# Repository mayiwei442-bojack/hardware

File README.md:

# ACID ALLOY / 酸性合金

多输入桌面控制器的外观设计、Blender 装配模型与交互展示网站。包含 13 个机械按键、旋钮、摇杆、触摸输入和 RGB 灯光的结构与展示资料。

## 项目文件

| 目录 | 内容 |
| --- | --- |
| [`website/`](website/) | 五章节产品展示网站、二维交互工作台、七步制作流程演示、测试与截图 |
| [`modeling/assets/`](modeling/assets/) | Blender 主模型、四种外观方案和阶段存档 |
| [`modeling/`](modeling/) | 渲染、印花贴图、建模脚本、尺寸参考、验收记录和操作说明 |
| [`device/`](device/) | 硬件设计、制造文件、打印模型、固件与配套工具 |

## Blender 方案

| 方案 | 文件 | 预览 |
| --- | --- | --- |
| 基础装配 | [`MacroPad.blend`](modeling/assets/MacroPad.blend) | 装配、器件和交互控制 |
| 酸性合金 | [`MacroPad_AcidAlloy.blend`](modeling/assets/MacroPad_AcidAlloy.blend) |  |
| 电光瓷器 | [`MacroPad_ElectricPorcelain.blend`](modeling/assets/MacroPad_ElectricPorcelain.blend) |  |
| 超频仪器 | [`MacroPad_OverclockInstrument.blend`](modeling/assets/MacroPad_OverclockInstrument.blend) |  |
| 反叛玩具 | [`MacroPad_RebelToy.blend`](modeling/assets/MacroPad_RebelToy.blend) |  |

使用 Blender 打开 `.blend` 文件；成品印花贴图已内嵌。历史验收记录保留当时的校验值和本机路径；可读项目名已统一替换，本次整理未重新执行 Blender 验收。

## 网站本地启动

```powershell
cd website
npm ci
npm run dev
```

浏览器打开 `http://localhost:3100`。网站目前以二维交互演示为主，正式 GLB、产品照片等素材的接入状态见 [`website/docs/assets.md`](website/docs/assets.md)。制作流程为浏览器内模拟。

## 制造资料

- [Gerber 制造文件](device/hw/v1/fab/keyboard-gerbers.zip)
- [BOM 元件清单](device/hw/v1/fab/keyboard-bom.csv)
- [SMT 贴片坐标](device/hw/v1/fab/keyboard-smt.csv)
- [打印与可编辑机械模型](device/hw/v1/mechanical/)
- [制造说明](device/hw/v1/fab/README.md)

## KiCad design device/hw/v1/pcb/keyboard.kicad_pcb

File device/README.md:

<picture>
  <source media="(prefers-color-scheme: dark)" srcset="site/public/assets/wordmark-dark.png">
  
</picture>

# keyboard

An open-source hardware recreation of OpenAI's **Codex Micro** macropad — 13 low-profile keys, a rotary encoder, an analog joystick, a capacitive touch pad, and per-key + underglow RGB on a wired USB-C board built around an STM32F072.

*The finished board — read the [launch post](https://github.com/mayiwei442-bojack/hardware/blog/keyboard-launch/) for the full story.*

**The PCB is written, not drawn.** The entire schematic is source code in [**CoHDL**](https://cohdl.org), an open-source, AI-native hardware description language. The compiler type-checks the design — units, pin-connection obligations, power integrity — and emits the netlist, BOM, footprints and layout constraints you can inspect under [`hw/v1/out/`](hw/v1/out/).

🌐 **https://github.com/mayiwei442-bojack/hardware** · 🖨️ **[Printable case on MakerWorld](https://makerworld.com/en/models/3163016-keyboard#profileId-3599737)** ([中国站](https://makerworld.com.cn/zh/models/2838721-keyboard-kai-yuan-jian-pan))

## Designed in CoHDL

This board was designed in [**CoHDL**](https://cohdl.org), an open-source hardware description language that makes schematic (PCB) design AI-native: a board is a program — typed, checked, and compiled. In CoHDL, the design in [`hw/v1/src/`](hw/v1/src/) *is* the schematic; the compiler is the oracle that grades it.

**CoHDL is open source.** Visit [cohdl.org](https://cohdl.org) to explore the language, or browse and contribute to the compiler and libraries on GitHub. This repository also checks in the complete compiler outputs under `hw/*/out/`, so the generated hardware design remains directly inspectable.

Questions about CoHDL, the hardware source, or building a board of your own? [Join the CoHDL and keyboard community on Discord](https://discord.gg/x7DXPvK66).

## What's inside

| Path | Contents |
|---|---|
| [`hw/v1/src/`](hw/v1/src/) | The PCB as CoHDL source: `main.cohdl` (top-level design), `keyboard_parts.cohdl` (datasheet-verified part bindings), `footprints.cohdl`, `pads.cohdl` |
| [`hw/v1/out/`](hw/v1/out/) | Checked-in compiler output: KiCad netlist (`keyboard.net`), BOM (`keyboard-bom.csv`), SMT placement (`keyboard-smt.csv`), `.kicad_mod` footprints, layout constraints (`keyboard-layout.json`) |
| [`hw/v1/pcb/`](hw/v1/pcb/) | The routed board — `keyboard.kicad_pcb` + KiCad project (design rules) |
| [`hw/v1/fab/`](hw/v1/fab/) | Manufacturing package: Gerber/drill zip, assembly BOM, SMT placement CSV — see [`hw/v1/fab/README.md`](hw/v1/fab/README.md) |
| [`hw/v1/mechanical/`](hw/v1/mechanical/) | Board outline (DXF) plus the printable enclosure parts — case, rotary knob, joystick cap, shipping tray and a solder-assembly jig, as editable Fusion 360 `.f3d` and ready-to-slice `.3mf`. Also published as a print profile on [MakerWorld](https://makerworld.com/en/models/3163016-keyboard#profileId-3599737) ([中国站](https://makerworld.com.cn/zh/models/2838721-keyboard-kai-yuan-jian-pan)) |
| [`hw/v1/docs/`](hw/v1/docs/) | Manufacturer datasheets for every active, connector, and electromechanical part in the BOM, with sourcing/verification notes — see [`hw/v1/docs/README.md`](hw/v1/docs/README.md) |
| [`layout/`](layout/) | The bootloader/firmware/host contract: flash and RAM map, image header, handoff words, HID update protocol, CRC-32 — `no_std`, shared by `fw`, `boot`, `app` and `scripts/` |
| [`boot/`](boot/) | Resident 24 KiB bootloader at 0x08000000: validates the application by length and CRC-32 before every start and offers a driverless USB HID update mode, so an interrupted update never bricks the pad. See [`boot/README.md`](boot/README.md) |
| [`fw/`](fw/) | Firmware — Rust + [embassy](https://embassy.dev) on STM32F072CB: key matrix, twin WS2812 chains, USB HID + vendor interface, driverless updates through the resident bootloader (ROM DFU kept for migration and recovery), and an opt-in **Codex Micro compat mode** (the pad boots with the Codex Micro's USB identity and speaks ChatGPT Desktop's device protocol so the desktop app drives it natively — confirmed with Codex desktop 26.825 on macOS). See [`fw/README.md`](fw/README.md) |
| [`app/`](app/) | Companion desktop app — Rust + [GPUI](https://gpui.rs), with a crisp 8-bit visual system: device dashboard, live connection state, and button-free firmware updates over USB. See [`app/README.md`](app/README.md) |

## Hardware (v1)

- **MCU:** STM32F072CBT6 (Cortex-M0), 8 MHz HSE crystal, 2×3 SWD debug socket
- **Keys:** 13× Kailh Choc V2 low-profile switches on a 19.05 mm grid (square 4×4-cell frame, matching the Codex Micro layout), 1N4148W per-key matrix diodes
- **Inputs:** EC11 rotary encoder, RKJXV analog joystick, capacitive touch pad
- **Lighting:** 13× per-key SK6812MINI-E (reverse-mount, one WS2812 chain) + 8× perimeter underglow SK6812MINI-E (second chain)
- **USB:** Type-C wired, USBLC6 ESD protection, AP2112 3.3 V LDO
- PCB laid out from the CoHDL-generated constraints; manufacturing handoff via IPC-2581

## Building

```sh
# Production firmware binary + debug ELF
scripts/build-firmware.sh dist

# Native GPUI macOS app bundle + DMG (ad-hoc signed for local testing)
scripts/package-macos.sh dist dist/keyboard-fw-<firmware-version>.bin

# Or run the companion app from source
cd app && cargo run --release --locked
```

On Windows, install Rust and Visual Studio's **Desktop development with C++**
workload, then build a portable package from PowerShell:

```powershell
rustup target add x86_64-pc-windows-msvc
./scripts/package-windows.ps1 `
  -OutputDir dist/windows `
  -FirmwareBin dist/keyboard-fw-<firmware-version>.bin `
  -Target x86_64-pc-windows-msvc
```

Use `aarch64-pc-windows-msvc` for a native Windows on Arm package; that build
also requires the Visual Studio LLVM/Clang component.

The open-source CoHDL compiler and its documentation are available at [cohdl.org](https://cohdl.org). Generated netlists, BOMs, footprints, and layout constraints remain checked in under `hw/*/out/` for inspection and use without rerunning the toolchain.

Releases build Intel and Apple Silicon DMGs, Windows x64 and Arm64 portable
ZIPs, and firmware through GitHub Actions. See
[`RELEASING.md`](RELEASING.md) for versioning, Apple signing/notarization
secrets, the required device smoke test, and the tag flow.
Linux packaging, USB permissions, and the STM32F072 ROM-DFU host-controller
workaround are tracked in
[`docs/linux-firmware-updates.md`](docs/linux-firmware-updates.md).

## Production files

The final routed v1 board lives in [`hw/v1/pcb/`](hw/v1/pcb/) (`keyboard.kicad_pcb`, opens in KiCad 9+). The manufacturing package — Gerber/drill zip, assembly BOM, and SMT pick-and-place CSV, ready to upload to a fab such as JLCPCB — is in [`hw/v1/fab/`](hw/v1/fab/), with DRC status and ordering notes in [`hw/v1/fab/README.md`](hw/v1/fab/README.md).

## Printing the case

The enclosure is published as a ready-to-print model on MakerWorld, alongside the editable Fusion sources in [`hw/v1/mechanical/`](hw/v1/mechanical/):

- **[MakerWorld — keyboard](https://makerworld.com/en/models/3163016-keyboard#profileId-3599737)**
- **[MakerWorld 中国 — keyboard 开源键盘](https://makerworld.com.cn/zh/models/2838721-keyboard-kai-yuan-jian-pan)**

The print covers the case, the rotary knob and the joystick cap, plus the solder-assembly jig and the shipping package as a bonus from the same project. Recommended settings: 0.4 mm nozzle, 0.2 mm layer height, 3 walls, 15–20% infill, PLA or PETG (PETG for a daily driver), **no supports required**.

Beyond the print you will need an assembled PCB, Choc V2-compatible keycaps, M2×4 female-female brass standoffs, M2×5 screws, and a USB-C cable.

---

*keyboard is an independent open-source project and is not affiliated with, endorsed by, or sponsored by OpenAI. "Codex Micro" refers to OpenAI's product; all trademarks belong to their respective owners.*

## 本仓库的发布配置

自动更新指向本仓库的 Releases；尚未发布清单时不会提供在线更新。macOS 打包使用本地 Sparkle 2.9.6 归档，通过 `SPARKLE_ARCHIVE` 指定文件，脚本仍会验证固定 SHA-256。

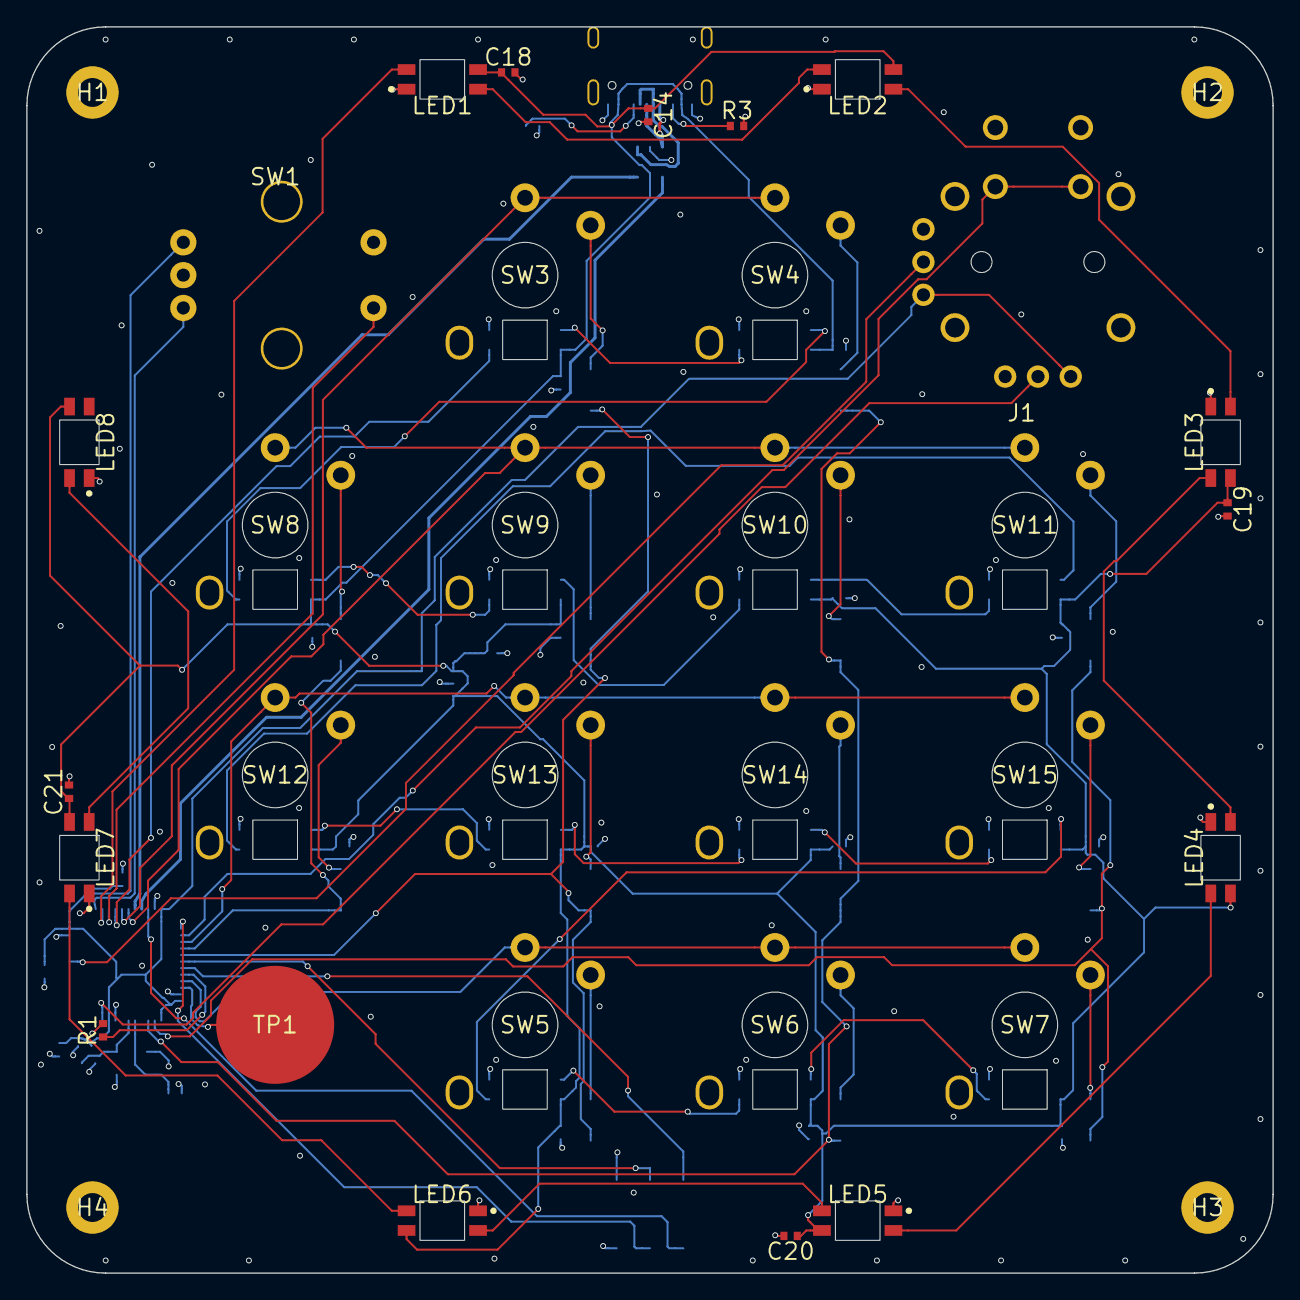
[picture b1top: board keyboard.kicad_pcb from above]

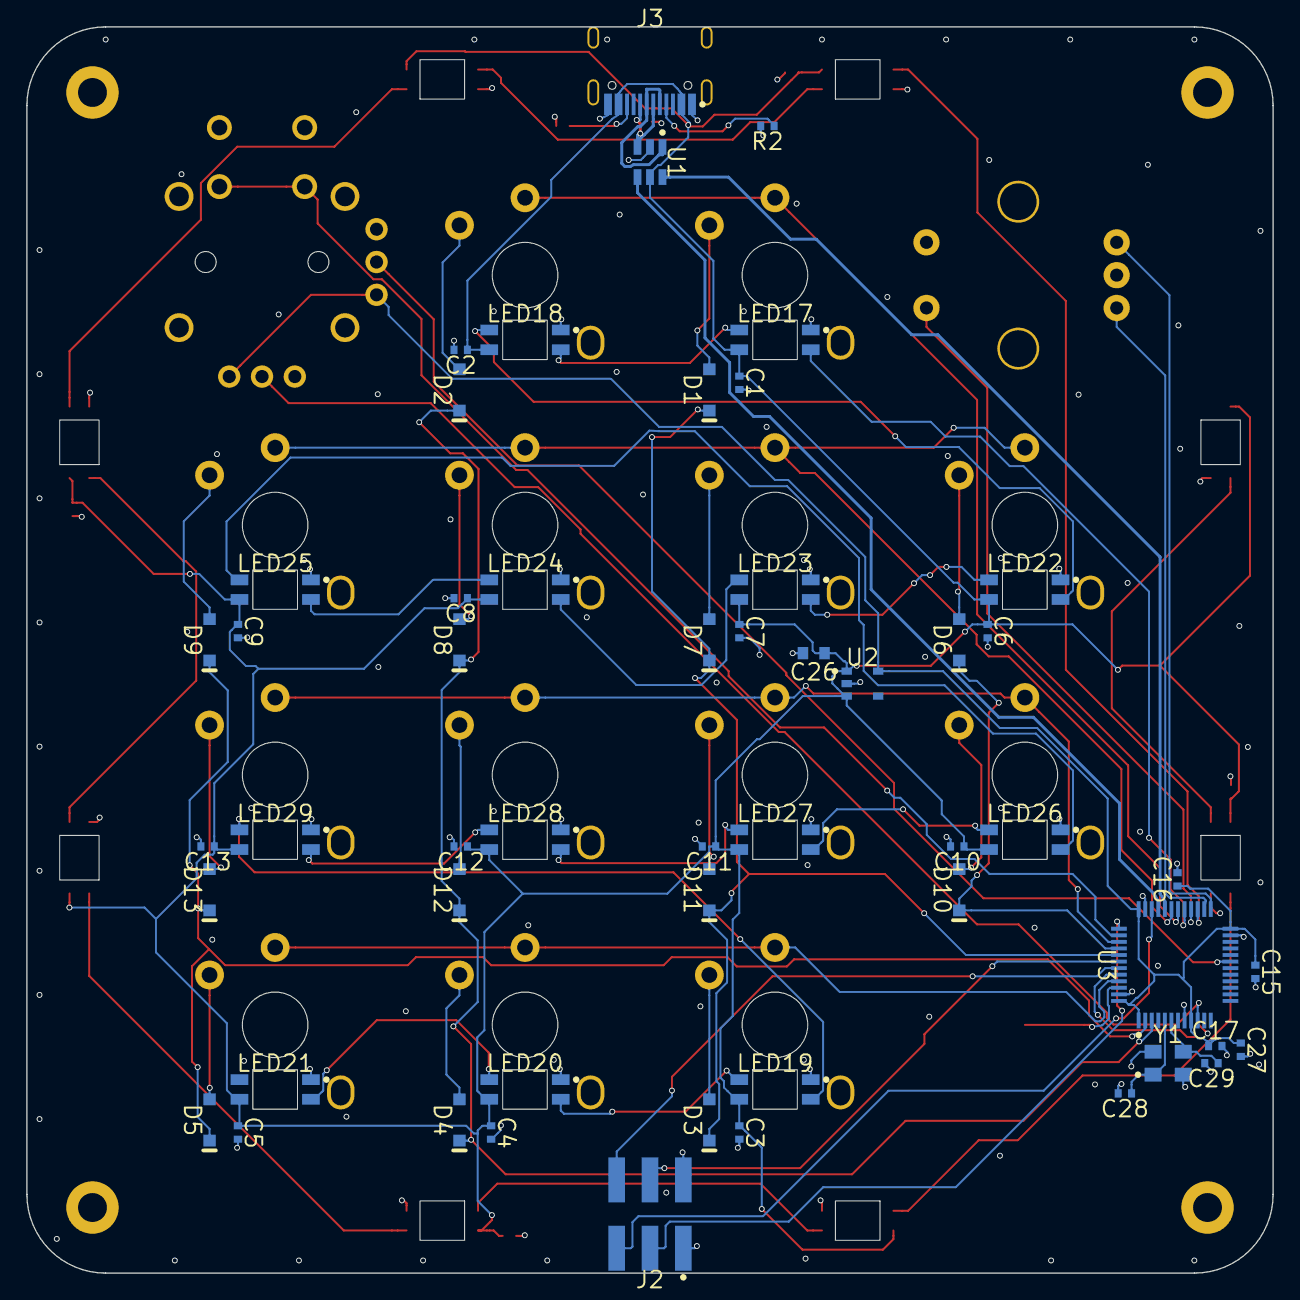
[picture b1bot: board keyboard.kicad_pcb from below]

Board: 4 copper layers, 95.0 x 95.0 mm, 88 parts (53 on the bottom side), 65 nets.

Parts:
C1, C2, C3, C4, C5, C6, C7, C8, C9, C10, C11, C12, C13, C14, C15, C16, C17, C18, C19, C20, C21: 100nF; passive-CHIP_0402
C26: 4.7uF; passive-CHIP_0603
C27: 1uF; passive-CHIP_0402
C28, C29: 15pF; passive-CHIP_0402
D1, D2, D3, D4, D5, D6, D7, D8, D9, D10, D11, D12, D13: Diode_1N4148; diode-FP_D_SOD_123
H1, H2, H3, H4: MountingHole; keyboard-FP_MountingHole_M2
J1: ThumbPointer; keyboard-FP_Joystick_RKJXV
J2: Socket_2x3; connectors-headers-smd_254-FP_Socket_2x3_254_SMD
J3: USB_C_Receptacle_2_0; usb-connectors-type_c-FP_USB_C_Receptacle_HRO_TYPE_C_31_M_12
LED1, LED2, LED3, LED4, LED5, LED6, LED7, LED8, LED17, LED18, LED19, LED20, LED21, LED22, LED23, LED24, LED25, LED26, LED27, LED28, LED29: SK6812; led-FP_LED_SK6812MINI_E
R1: 10kohm; passive-CHIP_0402
R2, R3: 5.1kohm; passive-CHIP_0402
SW1: RotaryEC11; keyboard-FP_Encoder_EC11
SW3, SW4, SW5, SW6, SW7, SW8, SW9, SW10, SW11, SW12, SW13, SW14, SW15: KeySwitch; keyboard-FP_SW_Choc_V2
TP1: CapTouchPad; keyboard-FP_TouchPad
U1: USBLC6; esd-FP_SOT_23_6
U2: AP2112K_3V3; ldo-SOT5P95X290X160N
U3: STM32F072CBT6; st_stm32-f0-stm32f072cb-QFP50P900X900X160_48N
Y1: Crystal8MHz; osc-FP_Crystal_3225

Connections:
BOOT0: R1.1, U3.44
CC1: J3.A5, R2.1
CC2: J3.B5, R3.1
COL0: D6.1, D10.1, U3.40
COL1: D1.1, D3.1, D7.1, D11.1, U3.41
COL2: D2.1, D4.1, D8.1, D12.1, U3.3
COL3: D5.1, D9.1, D13.1, U3.2
ENC_A: SW1.1, U3.25
ENC_B: SW1.3, U3.26
ENC_SW: SW1.4, U3.28
GND: C1.2, C2.2, C3.2, C4.2, C5.2, C6.2, C7.2, C8.2, C9.2, C10.2, C11.2, C12.2, C13.2, C14.2, C15.2, C16.2, C17.2, C18.2, C19.2, C20.2, C21.2, C26.2, C27.2, C28.2, C29.2, H1.1, H2.1, H3.1, H4.1, J1.A1, J1.B1, J1.L1, J1.L2, J1.L3, J1.L4, J1.SB, J1.SD, J2.1, J2.2, J3.A1, J3.A12, J3.B1, J3.B12, J3.SH1, J3.SH2, J3.SH3, J3.SH4, LED1.1, LED2.1, LED3.1, LED4.1, LED5.1, LED6.1, LED7.1, LED8.1, LED17.1, LED18.1, LED19.1, LED20.1, LED21.1, LED22.1, LED23.1, LED24.1, LED25.1, LED26.1, LED27.1, LED28.1, LED29.1, R1.2, R2.2, R3.2, SW1.2, SW1.5, SW1.6, SW1.7, U1.2, U2.2, U3.8, U3.23, U3.35, U3.47, Y1.2, Y1.4
HSE_IN: C28.1, U3.5, Y1.1
HSE_OUT: C29.1, U3.6, Y1.3
JOY_SW: J1.SA, J1.SC, U3.38
JOY_X: J1.A2, U3.19
JOY_Y: J1.B2, U3.10
KEY1: D1.2, SW3.2
KEY2: D2.2, SW4.2
KEY3: D6.2, SW8.2
KEY4: D7.2, SW9.2
KEY5: D8.2, SW10.2
KEY6: D9.2, SW11.2
KEY7: D10.2, SW12.2
KEY8: D11.2, SW13.2
KEY9: D12.2, SW14.2
KEY10: D13.2, SW15.2
KEY11: D3.2, SW5.2
KEY12: D4.2, SW6.2
KEY13: D5.2, SW7.2
LED_D0: LED17.2, U3.29
LED_D1: LED17.4, LED18.2
LED_D2: LED18.4, LED22.2
LED_D3: LED22.4, LED23.2
LED_D4: LED23.4, LED24.2
LED_D5: LED24.4, LED25.2
LED_D6: LED25.4, LED26.2
LED_D7: LED26.4, LED27.2
LED_D8: LED27.4, LED28.2
LED_D9: LED28.4, LED29.2
LED_D10: LED19.2, LED29.4
LED_D11: LED19.4, LED20.2
LED_D12: LED20.4, LED21.2
ROW0: SW3.1, SW4.1, U3.30
ROW1: SW8.1, SW9.1, SW10.1, SW11.1, U3.31
ROW2: SW12.1, SW13.1, SW14.1, SW15.1, U3.39
ROW3: SW5.1, SW6.1, SW7.1, U3.45
SWCLK: J2.3, U3.37
SWDIO: J2.5, U3.34
TOUCH: TP1.1, U3.46
UART_RX: J2.6, U3.43
UART_TX: J2.4, U3.42
UG_D0: LED1.2, U3.27
UG_D1: LED1.4, LED2.2
UG_D2: LED2.4, LED3.2
UG_D3: LED3.4, LED4.2
UG_D4: LED4.4, LED5.2
UG_D5: LED5.4, LED6.2
UG_D6: LED6.4, LED7.2
UG_D7: LED7.4, LED8.2
USBC_DM: J3.A7, J3.B7, U1.1
USBC_DP: J3.A6, J3.B6, U1.3
USB_DM: U1.6, U3.32
USB_DP: U1.4, U3.33
V3V3: C15.1, C16.1, C17.1, C27.1, J1.A3, J1.B3, U2.5, U3.1, U3.9, U3.24, U3.36, U3.48
VBUS: C1.1, C2.1, C3.1, C4.1, C5.1, C6.1, C7.1, C8.1, C9.1, C10.1, C11.1, C12.1, C13.1, C14.1, C18.1, C19.1, C20.1, C21.1, C26.1, J3.A4, J3.A9, J3.B4, J3.B9, LED1.3, LED2.3, LED3.3, LED4.3, LED5.3, LED6.3, LED7.3, LED8.3, LED17.3, LED18.3, LED19.3, LED20.3, LED21.3, LED22.3, LED23.3, LED24.3, LED25.3, LED26.3, LED27.3, LED28.3, LED29.3, U1.5, U2.1, U2.3

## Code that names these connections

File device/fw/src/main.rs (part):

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//! the position-aware GPIO assignment) — if the .cohdl changes, this table is
//! the one to update:
//!
//!   ROW0..3  = PA9  PA10 PB3  PB8   (outputs, drive high per scan step)
//!   COL0..3  = PB4  PB5  PC14 PC13  (inputs, pull-down; diode cathode -> COL)
//!   ENC_A/B  = PB12 PB13 (quadrature, pull-up, common to GND)
//!   ENC_SW   = PB15      (pull-up, active low)
//!   JOY_X/Y  = PB1/ADC_IN9  PA0/ADC_IN0 (stick mounted rotated: the JOY_X
//!              net senses vertical travel — adc_task swaps the channels)
//!   JOY_SW   = PA15      (pull-up, active low; DEAD on the 2026-08 fab —
//!              that revision's footprint paired the switch poles by column
//!              instead of by row, shorting the line to GND through the
//!              switch body; fixed in keyboard_parts.cohdl for the next spin)
//!   TOUCH    = PB9       (RC charge-time sensing, no external R)
//!   LED_KEY  = PA8       (13x SK6812MINI-E per-key chain)
//!   LED_UG   = PB14      (8x SK6812MINI-E perimeter underglow ring)
//!
//! COL2/COL3 sit on PC14/PC13, which are behind the VBAT power switch and can
//! only source a few mA. That is fine here and deliberate: in COL2ROW the
//! columns are only ever READ. Do not move an output onto them.
//!   USB      = PA11/PA12 (FS device; HSI48 + CRS, crystal not required)
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//! The `proto` Cargo feature selects the PROTOTYPE pin map instead — boards
//! fabbed before the 2026-07-28 GPIO re-derivation: rows PA9 PB3 PB6 PB5,
//! cols PB8 PB7 PA15 PA10, encoder PC13/PC14/PC15, joystick push PA8,
//! JOY_Y PB0/ADC_IN8, per-key chain PB4, 16-LED underglow ring on PA0.
//! Touch, USB, and SWD are identical on both revisions.
//!
//! HID map: every input's emitted code is CONFIGURABLE and stored in flash
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});

// ---- board revision (see the pin-map tables in the module docs) ----
// JOY_Y is the one pin that crosses an ADC channel between revisions, so it
// is the one place the peripheral TYPE differs; everything else is erased
// into Output/Input/ExtiInput at construction.
#[cfg(not(feature = "proto"))]
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
    // ---- joystick ADC ----
    let adc = Adc::new(p.ADC1, Irqs);
    let joy_x = p.PB1;
    #[cfg(not(feature = "proto"))]
    let joy_y = p.PA0;
    #[cfg(feature = "proto")]
    let joy_y = p.PB0;

    // ---- touch (RC charge-time on PB9) ----
    let touch = Flex::new(p.PB9);

    // ---- LED chains ----
    #[cfg(not(feature = "proto"))]
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        if s == state {
            continue;
        }
        // Negated: the board's ENC_A/ENC_B pin ordering runs opposite the
        // table's sense, so without this a clockwise turn counts negative.
        let delta = -QUAD_LUT[((state << 2) | s) as usize];
        debug!(
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#[embassy_executor::task]
async fn adc_task(
    mut adc: Adc<'static, peripherals::ADC1>,
    mut joy_x: peripherals::PB1,
    mut joy_y: JoyYPin,
) {
    info!("adc_task: entered");
    let mut ticker = Ticker::every(Duration::from_millis(20));
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        ticker.next().await;
        let a = adc.read(&mut joy_x).await;
        let b = adc.read(&mut joy_y).await;
        // The current board mounts the stick rotated, so the JOY_X net (PB1)
        // senses the stick's VERTICAL travel and PA0 the horizontal. Swap at
        // the source so (x, y) mean what they say for keys and mouse alike.
        #[cfg(not(feature = "proto"))]
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    }
}

/// Cap-touch on PB9 by RC charge time: discharge the pad, release it to the
/// internal pull-up, and count polls until the input reads high. A finger adds
/// capacitance -> longer rise. Self-calibrates a floating baseline.
///
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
